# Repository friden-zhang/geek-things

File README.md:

# geek-things

Hardware design monorepo built around atopile.

## Layout

- `hardware/boards/`: one standalone atopile project per board family member
- `hardware/packages/`: reusable internal hardware building blocks
- `hardware/contracts/`: board contracts consumed by firmware and host-side tools
- `firmware/`: board-specific and shared embedded code
- `software/tools/`: bring-up, manufacturing, and test tooling
- `docs/architecture/`: repository conventions and release rules
- `tools/ci/`: structure checks and CI helpers

## Current Board

- `hardware/boards/esp32s3_devkit`: USB-C powered ESP32-S3 development board
- Reusable packages extracted from this board:
  - `hardware/packages/power/usb_c_5v_input.ato`
  - `hardware/packages/power/ap2112k_3v3_ldo.ato`
  - `hardware/packages/common/esp32s3_module_core.ato`
  - `hardware/packages/common/esp32s3_devkit_io.ato`

## Compiler Development

The `atopile` compiler is vendored as a git submodule at `third_party/atopile`.

```bash
git submodule update --init --recursive
uv sync --locked --python 3.14
```

## Common Commands

```bash
uv sync
uv run python tools/ci/monorepo.py --check
uv run python tools/ci/monorepo.py --json-boards
uv run python tools/ci/monorepo.py --build-board esp32s3_devkit
uv run python tools/ci/monorepo.py --build-board esp32s3_devkit --frozen
```

Successful `ato build` runs now produce:

- `layouts/default/default.kicad_pcb`
- `build/builds/default/default.canonical_design.json`

Paths are relative to each board directory under `hardware/boards/<board>/`.

Build a board directly from its project directory:

```bash
cd hardware/boards/esp32s3_devkit
uv run ato build
uv run ato build --frozen
```

## KiCad Layout Safety

`uv run python tools/ci/monorepo.py --build-board <board>` and `uv run ato build`
update the board's checked-in `layouts/default/default.kicad_pcb` in place.
That file is a layout source file, not a disposable build artifact.

If you edited the PCB manually in KiCad, a later build may rewrite parts of that
layout when the `.ato` design changes. The usual risk points are:

- adding or removing footprints
- changing instance names or hierarchy in `.ato`
- changing nets, picked parts, or footprints
- letting atopile re-apply board appearance and managed layout state

Recommended workflow before rebuilding a board with manual KiCad edits:

1. Commit or otherwise checkpoint `layouts/default/default.kicad_pcb`.
2. Run a frozen check first:

```bash
uv run python tools/ci/monorepo.py --build-board esp32s3_devkit --frozen
```

3. If frozen mode reports layout changes, inspect the difference before running a
   normal build.
4. If you decide the update is acceptable, rerun without `--frozen`.

Notes:

- `--frozen` is only meaningful for `--build-board` and `--build-all`.
- Regular `--build-board` will still back up the previous layout under
  `hardware/boards/<board>/build/builds/default/backups/`.
- Even when builds succeed, treat large `.ato` refactors after manual routing as
  potentially layout-destructive until reviewed.

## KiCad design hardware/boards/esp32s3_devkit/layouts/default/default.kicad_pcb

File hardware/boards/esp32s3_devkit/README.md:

# esp32s3_devkit

USB-C powered ESP32-S3 development board built from reusable package blocks.

## Features

- ESP32-S3-WROOM-1 core with default I2C, SPI, UART, and native USB assignments
- USB-C sink-side input front-end via the upstream `atopile/usb-connectors` package
- BOOT, RESET, and USER buttons
- WS2812B-2020 addressable RGB status LED

## Build

```bash
ato build
```

Run the command from `hardware/boards/esp32s3_devkit/`.

## Notes

- The board-level `3V3` rail is generated by a concrete `AP2112K-3.3TRG1` LDO package.
- The board contract is the source of truth for default bus names and occupied GPIO assignments.

## Companion Files

- contract: `hardware/contracts/esp32s3_devkit.yaml`
- firmware target: `firmware/boards/esp32s3_devkit/`

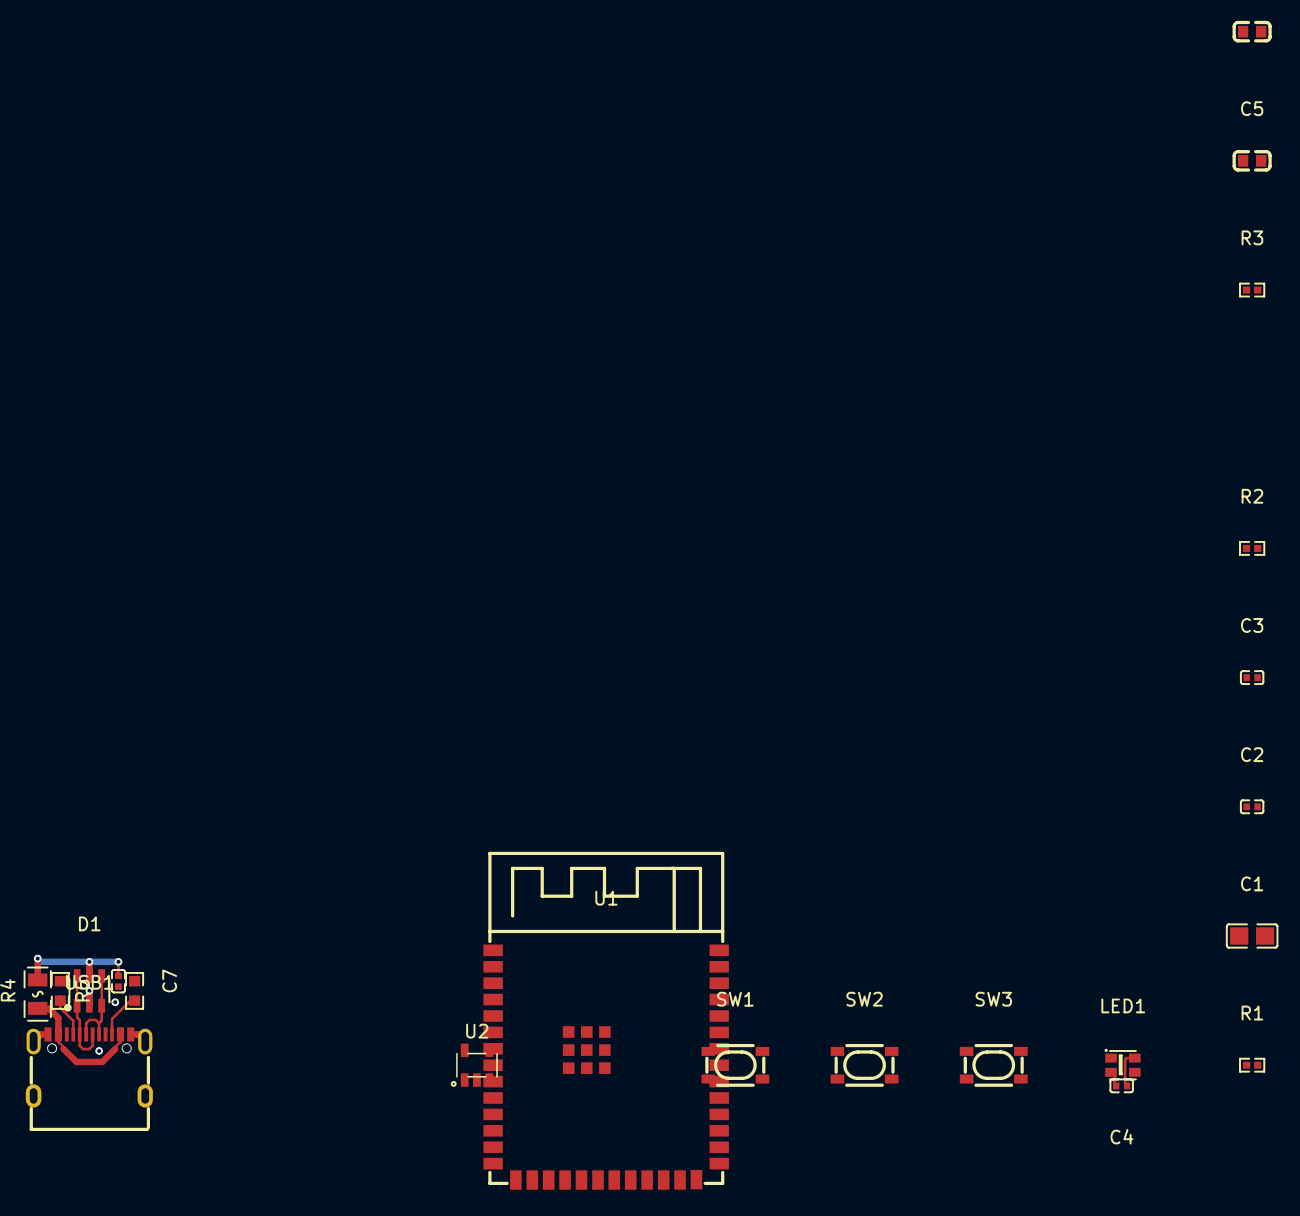
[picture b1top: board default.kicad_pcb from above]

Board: 2 copper layers, 21 parts (0 on the bottom side), 12 nets.

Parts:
C1: 10µF; C0805
C2, C4, C7: 100nF; C0402
C3: 1µF; C0402
C5, C6: 1µF; C0603
D1: SOT-23-6_L2.9-W1.6-P0.95-LS2.8-BL
F1: F0805
LED1: LED-SMD_4P-L2.0-W2.0-TL_WS2812B-2020
R1, R2, R3: 10kΩ; R0402
R4, R5: 10kΩ; R0603
SW1, SW2, SW3: KEY-SMD_4P-L4.2-W3.2-P2.20-LS4.6
U1: WIRELM-SMD_ESP32-S3-WROOM-1
U2: SOT-25-5_L2.9-W1.6-P0.95-LS2.8-BL
USB1: USB-C-SMD_TYPE-C-6PIN-2MD-073

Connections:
DATA_N: D1.1, D1.6, U1.13, USB1.5, USB1.7
DATA_P: D1.3, D1.4, U1.14, USB1.6, USB1.8
c_en-power-hv: C3.1, R2.2, SW2.1, SW2.2, U1.3
cc[0]-4: R4.1, USB1.4
cc[1]-10: R5.1, USB1.10
data_in-line: LED1.3, U1.25
hv: C1.1, C2.1, C4.1, C6.1, LED1.4, R1.1, R2.1, R3.1, U1.2, U2.5
input: R1.2, SW1.1, SW1.2, U1.27
lv: C1.2, C2.2, C3.2, C4.2, C5.2, C6.2, C7.2, D1.2, LED1.2, R4.2, R5.2, SW1.3, SW1.4, SW2.3, SW2.4, SW3.3, SW3.4, U1.1, U1.40, U1.41, U2.1, USB1.1, USB1.12, USB1.13, USB1.14, USB1.15, USB1.16
power_vbus-hv: F1.1, USB1.2, USB1.11
user_button-input: R3.2, SW3.1, SW3.2, U1.24
vbus_5v-hv: C5.1, C7.1, D1.5, F1.2, U2.2, U2.3

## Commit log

2026-04-08 chore: add .gitignore
2026-04-08 feat(monorepo): scaffold atopile hardware workspace
    Restructure the repo around per-board atopile projects so hardware, firmware, and host tooling can share one versioned tree. Add validation and CI entry points so boards can be discovered and built c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
    Made-with: Cursor
2026-04-09 feat(esp32s3-devkit): add first reusable board stack
    Replace the placeholder app board with a real ESP32-S3 devkit and extract reusable USB-C power, 3V3 LDO, MCU core, and devkit I/O packages so future boards can share the same hardware building blocks.
    Adopt uv-managed project commands and document frozen layout checks so KiCad changes stay reviewable as the board evolves.
    Made-with: Cursor
2026-04-10 # docs(esp32s3-devkit): clarify reusable board wiring
    Made-with: Cursor
    #
    # Document how power, USB, boot, and GPIO nets are divided between the board and shared packages so the ESP32-S3 stack is easier to compose and review.
2026-04-10 docs(atopile-easyeda-pro): define phase 1 foundation
    Capture the agreed architecture for integrating the forked compiler and introducing canonical IR and stable IDs before backend work begins.
    This keeps EasyEDA Pro support and controlled round-trip anchored in compiler contracts instead of monorepo-local adapters.
    Made-with: Cursor
2026-04-11 feat(monorepo): vendor atopile canonical build foundation
    Wire the forked atopile compiler into local development and CI so board builds emit canonical design snapshots and backend sidecars from compiler-owned contracts.
    This also validates the new foundation against esp32s3_devkit and keeps the resulting KiCad layout update alongside the successful build outputs.
    Made-with: Cursor
2026-04-11 fix(monorepo): lock runtime support for vendored atopile
    Update the editable compiler lock state so fresh main-branch environments install the tooling needed to run the vendored atopile build path.
    This keeps merged local checkouts reproducible without depending on stale virtualenv state from the feature worktree.
    Made-with: Cursor
2026-04-11 chore(atopile): bump submodule for EasyEDA Pro phase-2 shell export
    Points third_party/atopile at easyeda-pro-phase2-native-export: optional
    ato build -t easyeda-pro-export emits layouts/easyeda_pro/<variant>/ bundle.
    Made-with: Cursor
2026-04-11 chore(gitignore): ignore generated EasyEDA Pro layout exports
    Made-with: Cursor
2026-04-11 chore(atopile): bump submodule for EasyEDA project.json boards fix
    Made-with: Cursor
2026-04-11 chore(atopile): bump submodule for -t only and early canonical snapshot
    Made-with: Cursor
2026-04-11 chore(atopile): bump submodule for EasyEDA empty shell fixture
    Made-with: Cursor
2026-04-12 chore(atopile): bump submodule for native export phase2
    Track latest easyeda-pro-phase2-native-export and add superpowers plan notes.
    Made-with: Cursor
2026-04-12 feat(hardware): wire esp32s3 contract outline into atopile export
    Add layout.board_outline_mm to the board hardware contract and
    paths.hardware-contract in ato.yaml. Bump atopile submodule for
    EasyEDA Pro PCB net/outline enrichment, schematic logical-net ATTRs,
    and contract YAML parsing for canonical physical intent.
    Made-with: Cursor
2026-04-12 chore(atopile): bump submodule for native PCB COMPONENT+PAD export
    Made-with: Cursor
2026-04-12 chore(atopile): bump submodule for PAD_NET / pad_nets IR
    Made-with: Cursor
2026-04-12 chore: bump atopile submodule for EasyEDA Pro export fixes
    Includes manifest schema and JLCEDA-aligned bundle (project.json, efoo, esch).
    Made-with: Cursor
